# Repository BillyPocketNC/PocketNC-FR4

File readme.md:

# Support for this Project has been discontinued
This is an open source project and is not commercially supported.

For more information and files see [our Wiki](https://pocketnc.atlassian.net/wiki/spaces/PNFUR/pages/368902363/FR4+Resources) for more information

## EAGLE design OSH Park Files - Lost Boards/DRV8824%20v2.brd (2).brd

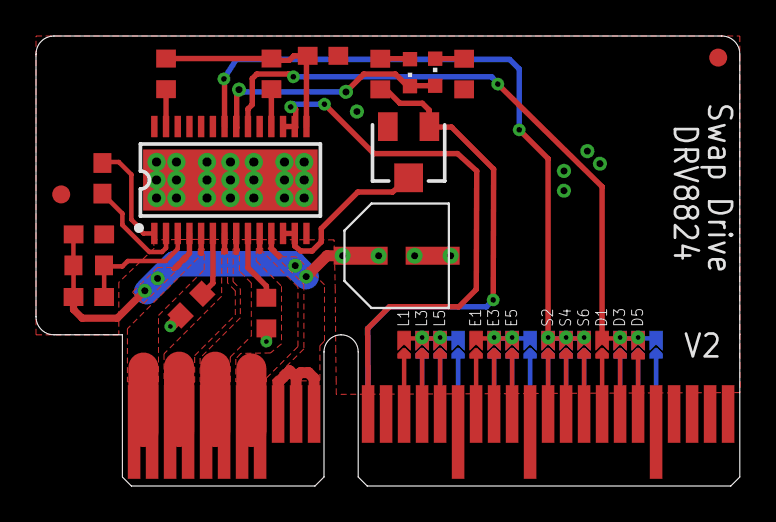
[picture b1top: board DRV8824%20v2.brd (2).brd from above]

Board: 2 copper layers, 39.1 x 25.0 mm, 19 parts (0 on the bottom side), 22 nets.

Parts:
BLU1: CHIPLED_0603
C3: 4.7uf; C0603
C9: .01uf; C0603
C10, C11: .1uf; C0603
DRV8824: DRV8824; HTSSOP-28
GRN1: CHIPLED_0603
R1, R9: 460; R0603
R2, R3: 10k; R0603
R4: .33 ohm; R0603
R5: .33ohm; R0603
R6: 1m; R0603
R22: 10K; TRIMPOT-3MM-2
U$2: PCIE_64_SMART_BOARD
U$7: EEEFK0J220R
U$9, U$12: FIDUCIAL; FIDUCIAL_1MM

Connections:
3.3V: C3.1, DRV8824.15, R2.2, R3.2
3V: R1.2, R22.1, U$2.P$12
5V: DRV8824.16, DRV8824.17, U$2.P$44
DIR: DRV8824.20, U$2.P$57@1
ENBL: BLU1.A, DRV8824.21, GRN1.C
GND: C3.2, C10.2, DRV8824.14, DRV8824.28, DRV8824.GND@10, DRV8824.GND@11, DRV8824.GND@12, DRV8824.GND@13, DRV8824.GND@14, DRV8824.GND@15, DRV8824.GND@16, DRV8824.GND@17, DRV8824.GND@18, DRV8824.GND@19, DRV8824.GND@20, DRV8824.GND@21, DRV8824.GND@22, DRV8824.GND@23, DRV8824.GND@24, DRV8824.GND@25, DRV8824.GND@26, DRV8824.GND@27, DRV8824.GND@28, DRV8824.GND@29, DRV8824.GND@30, DRV8824.GND@PAD, R4.1, R5.1, R9.2, R22.3, U$2.GND@1, U$2.GND@2, U$2.GND@3, U$2.P$13, U$2.P$25, U$2.P$49, U$2.P$53, U$2.P$60, U$7.GND@1, U$7.GND@2, U$7.GND@3
unnamed: C9.2, DRV8824.1
unnamed: C9.1, DRV8824.2
unnamed: DRV8824.18, R2.1
unnamed: DRV8824.9, R5.2
unnamed: DRV8824.6, R4.2
unnamed: BLU1.C, R9.1
unnamed: GRN1.A, R1.1
unnamed: DRV8824.12, DRV8824.13, R22.2
unnamed: DRV8824.27, R3.1
PHASE1: DRV8824.5, U$2.P$33, U$2.P$34
PHASE2: DRV8824.7, U$2.P$35, U$2.P$36
PHASE3: DRV8824.8, U$2.P$37, U$2.P$38
PHASE4: DRV8824.10, U$2.P$39, U$2.P$40
STEP: DRV8824.22, U$2.P$22@1
VCC: C10.1, C11.1, DRV8824.4, DRV8824.11, R6.1, U$2.VCC@1, U$2.VCC@2, U$2.VCC@3, U$7.P$1, U$7.P$3, U$7.P$5
VCP: C11.2, DRV8824.3, R6.2

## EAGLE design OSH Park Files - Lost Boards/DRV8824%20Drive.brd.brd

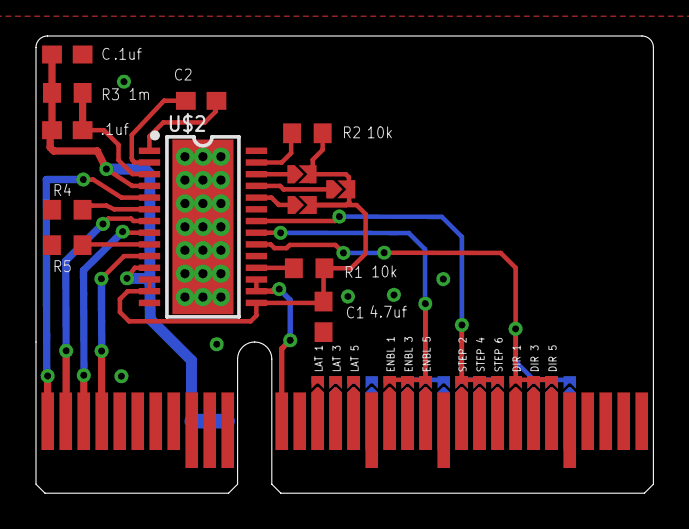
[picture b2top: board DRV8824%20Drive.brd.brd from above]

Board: 2 copper layers, 34.3 x 25.4 mm, 14 parts (0 on the bottom side), 22 nets.

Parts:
10NF2: .1uf; C0603
C: .1uf; C0603
C1: 4.7uf; C0603
C2: .01uf; C0603
R1, R2: 10k; R0603
R3: 1m; R0603
R4, R5: R0603
U$1: PCIE_64_SMART_BOARD
U$2: DRV8824; HTSSOP-28
U$3, U$4, U$5: SELECTIVE_CONNECT

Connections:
3.3V: C1.1, U$2.12, U$2.13, U$2.15
3V: R1.2, R2.2, U$3.P$2, U$4.P$2, U$5.P$2
5V: U$1.P$44, U$2.16, U$2.17
A1: U$1.P$33, U$2.5
A2: U$1.P$34, U$2.7
B1: U$1.P$36, U$2.10
B2: U$1.P$35, U$2.8
DIR: U$1.P$26@1, U$1.P$27@1, U$1.P$28@1, U$1.P$57@1, U$1.P$58@1, U$1.P$59@1, U$2.20
ENBL: U$1.P$19@1, U$1.P$20@1, U$1.P$21@1, U$1.P$50@1, U$1.P$51@1, U$1.P$52@1, U$2.21
GND: C.2, C1.2, R4.1, R5.1, U$1.GND@1, U$1.GND@2, U$1.GND@3, U$1.P$13, U$1.P$25, U$1.P$49, U$1.P$53, U$1.P$60, U$2.14, U$2.28, U$2.GND@10, U$2.GND@11, U$2.GND@12, U$2.GND@13, U$2.GND@14, U$2.GND@15, U$2.GND@16, U$2.GND@17, U$2.GND@18, U$2.GND@19, U$2.GND@20, U$2.GND@21, U$2.GND@22, U$2.GND@23, U$2.GND@24, U$2.GND@25, U$2.GND@26, U$2.GND@27, U$2.GND@28, U$2.GND@29, U$2.GND@30, U$2.GND@PAD
unnamed: C2.2, U$2.1
unnamed: C2.1, U$2.2
unnamed: R5.2, U$2.9
unnamed: R1.1, U$2.18
unnamed: R4.2, U$2.6
unnamed: R2.1, U$2.27
unnamed: U$2.26, U$3.P$1
unnamed: U$2.25, U$4.P$1
unnamed: U$2.24, U$5.P$1
STEP: U$1.P$22@1, U$1.P$23@1, U$1.P$24@1, U$1.P$54@1, U$1.P$55@1, U$1.P$56@1, U$2.22
VCC: 10NF2.1, C.1, R3.1, U$1.P$9, U$1.P$10, U$1.P$11, U$2.4, U$2.11
VCP: 10NF2.2, R3.2, U$2.3

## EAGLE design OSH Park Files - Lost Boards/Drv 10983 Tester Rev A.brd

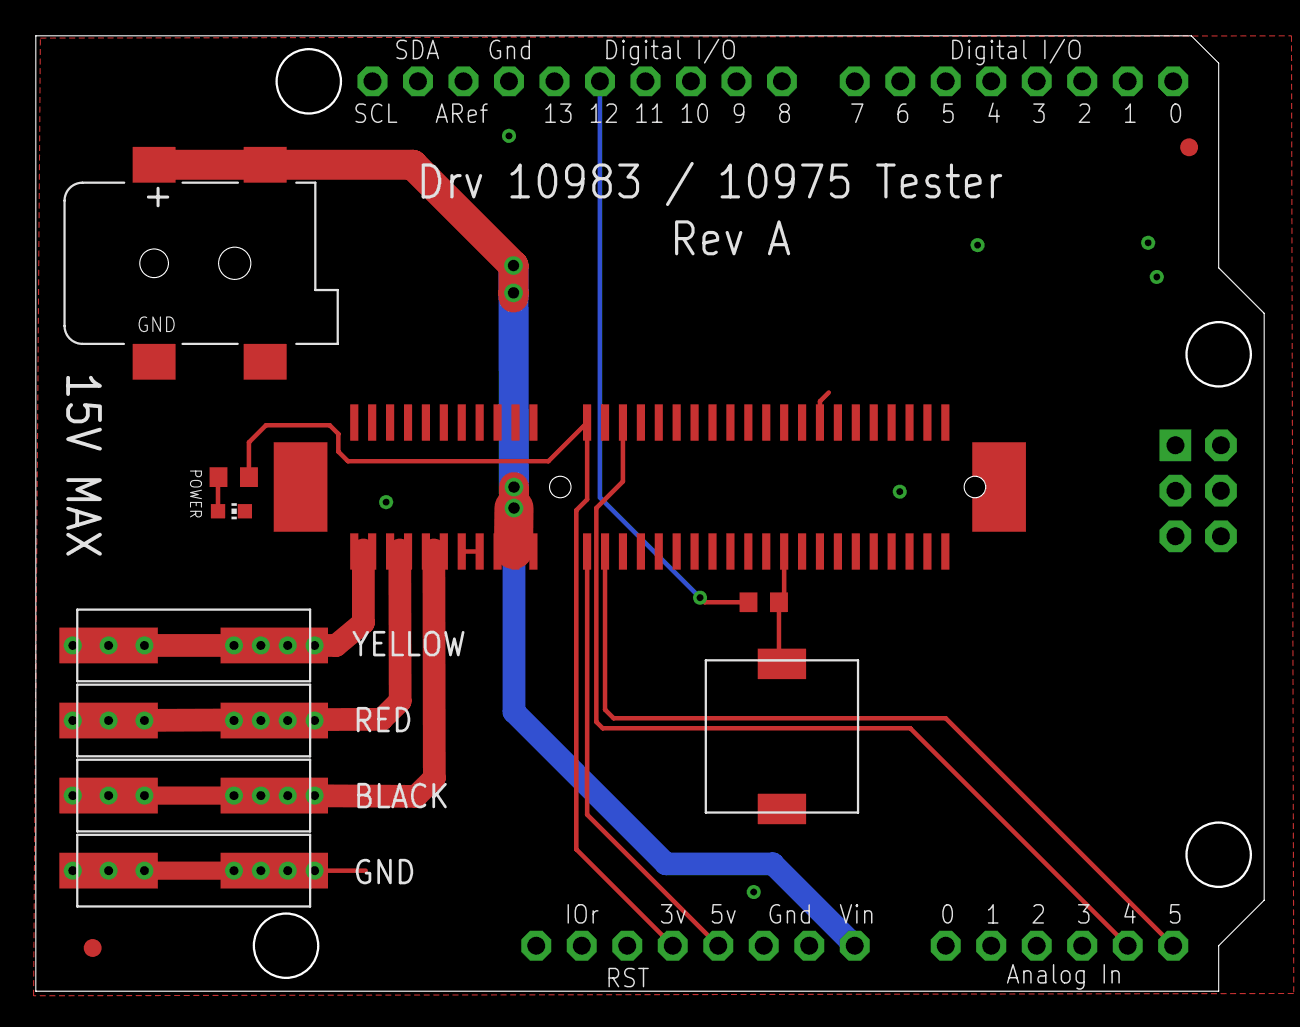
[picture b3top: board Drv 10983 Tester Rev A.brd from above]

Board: 2 copper layers, 68.5 x 53.2 mm, 13 parts (0 on the bottom side), 13 nets.

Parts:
BLACK: 104188-0110
CN1: DCJACK_2MM_SMT
GND: 104188-0110
M2: ARDUINO_R3_ICSP; ARDUINOR3_ICSP
POWER: CHIP-LED0603
R1: 460; R0603
R2: 220; R0603
RED: 104188-0110
U$1: 10061913-101CLF; 10076266-100CLF
U$2, U$3: FIDUCIAL; FIDUCIAL_1MM
U$4: BUTTON_SKSTAAE010
YELLOW: 104188-0110

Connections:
3V: M2.3V, R1.1, U$1.P$12
5V: M2.5V, U$1.P$44
ENBL: R2.1, U$1.P$55, U$4.P$1
GND: CN1.GND, CN1.GNDBREAK, GND.1@1, M2.GND, M2.GND@1, M2.GND@3, POWER.C, U$1.P$9, U$1.P$10, U$1.P$11, U$1.P$13, U$1.P$25, U$1.P$49, U$1.P$53, U$1.P$60, U$4.P$2
unnamed: POWER.A, R1.2
unnamed: M2.D12, R2.2
O: U$1.P$39, U$1.P$40
SCL: M2.A5, U$1.P$45
SDA: M2.A4, U$1.P$14
U: U$1.P$33, U$1.P$34, YELLOW.1@1
V: RED.1@1, U$1.P$35, U$1.P$36
VCC: CN1.PWR1, M2.VIN, U$1.P$41, U$1.P$42, U$1.P$43
W: BLACK.1@1, U$1.P$37, U$1.P$38

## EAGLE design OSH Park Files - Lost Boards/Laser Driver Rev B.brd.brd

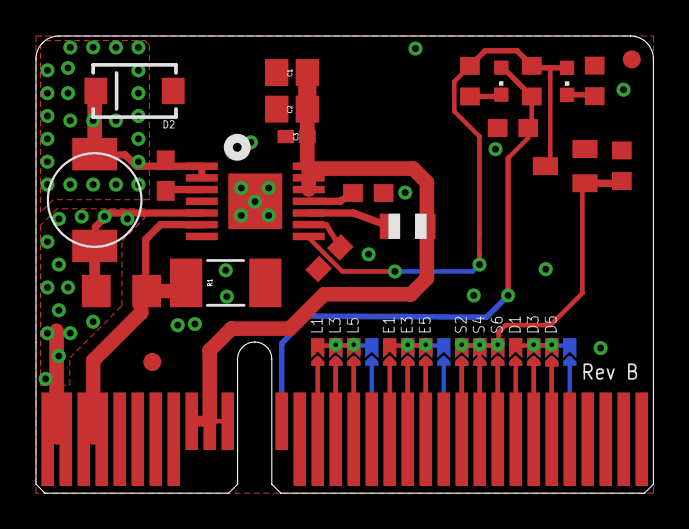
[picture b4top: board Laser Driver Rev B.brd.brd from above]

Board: 2 copper layers, 34.3 x 25.4 mm, 23 parts (0 on the bottom side), 14 nets.

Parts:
2N7002P: SOT23
C1, C2: 10uf; C0805
C3: C0402K
C11: .1uf; C0603
CB: 22nf; C0603
CC: 100nf; C0603
CF: 100nf; C0603
CO: C1206
D2: B340A; SMA-DIODE
GRN: CHIPLED_0603
R1: .166; R2010
R3, R7, R9: 460; R0603
R6: 10k; R0603
R-ON: 148k; R0805
RED: CHIPLED_0603
U$1: LM3406; HTSSOP-14
U$2: PCIE_64_SMART_BOARD
U$5, U$6: FIDUCIAL; FIDUCIAL_1MM
U$7: L-13uH; LQH55

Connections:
3V: C11.2, GRN.A, R7.2, U$2.P$12
ENBL-IN: 2N7002P.1, R6.2, U$2.P$22@1
ENBL-OUT: 2N7002P.3, R7.1, R9.2, RED.A, U$1.P$8
GND: 2N7002P.2, C1.2, C2.2, C3.2, C11.1, CC.1, CF.1, D2.A, R1.1, R3.2, R6.1, U$1.P$7, U$1.P$15, U$2.GND@1, U$2.GND@2, U$2.GND@3, U$2.P$13, U$2.P$25, U$2.P$49, U$2.P$53, U$2.P$60
LS+: CO.1, U$1.P$5, U$2.P$33, U$2.P$34, U$7.2
LS-: CO.2, R1.2, U$1.P$6, U$2.P$35, U$2.P$36
unnamed: CB.1, U$1.P$3
unnamed: GRN.C, R9.1
unnamed: R3.1, RED.C
unnamed: CC.2, U$1.P$9
unnamed: CF.2, U$1.P$11
RON: R-ON.1, U$1.P$10
SW: CB.2, D2.C, U$1.P$1, U$1.P$2, U$7.1
VCC: C1.1, C2.1, C3.1, R-ON.2, U$1.P$12, U$1.P$13, U$1.P$14, U$2.VCC@1, U$2.VCC@2, U$2.VCC@3

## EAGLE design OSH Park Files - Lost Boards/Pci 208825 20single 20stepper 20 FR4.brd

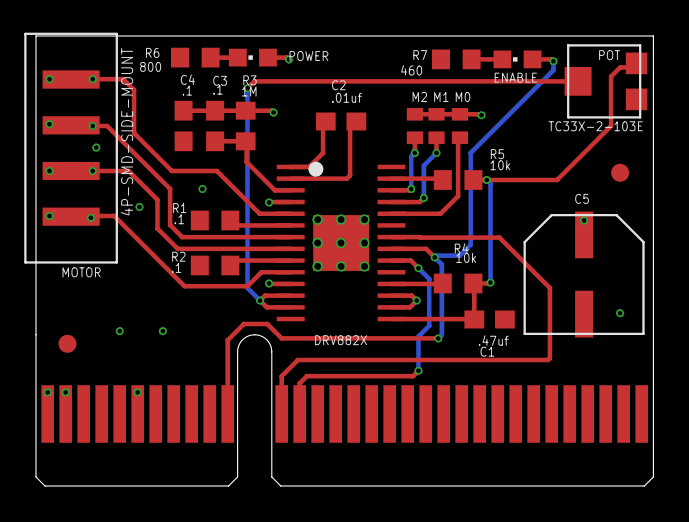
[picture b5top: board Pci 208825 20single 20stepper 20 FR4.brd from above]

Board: 4 copper layers, 34.3 x 25.0 mm, 23 parts (0 on the bottom side), 24 nets.

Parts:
C1: .47uf; C0603
C2: .01uf; C0603
C3, C4: .1; C0603
C5: EEEFTH101XAP
DRV882X: DRV8825
ENABLE: CHIPLED_0603
M0, M1, M2: R0402
MOTOR: 4P-SMD-SIDE-MOUNT
POT: TC33X-2-103E
POWER: CHIPLED_0603
R1, R2: .1; R0603
R3: 1M; R0603
R4, R5: 10k; R0603
R6: 800; R0603
R7: 460; R0603
U$1: 64P-PCI-EXPRESS
U$2, U$3: FIDUCIAL; FIDUCIAL_1MM

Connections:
+3.3V: C1.1, DRV882X.P$15, POT.P$2, R4.2, R5.2
+5V: DRV882X.P$16, DRV882X.P$17, M0.2, M1.2, M2.2, POWER.A, U$1.P$6, U$1.P$59
A1: DRV882X.P$5, MOTOR.P$1
A2: DRV882X.P$7, MOTOR.P$2
B1: DRV882X.P$10, MOTOR.P$4
B2: DRV882X.P$8, MOTOR.P$3
DIR: DRV882X.P$20, U$1.P$13
ENBL1: DRV882X.P$21, ENABLE.A, U$1.P$11
GND: C1.2, C4.2, C5.P$2, DRV882X.GND, DRV882X.GND@1, DRV882X.GND@2, DRV882X.GND@4, DRV882X.GND@5, DRV882X.GND@6, DRV882X.GND@7, DRV882X.GND@8, DRV882X.GND@9, DRV882X.P$14, DRV882X.P$28, DRV882X.P$29, POT.P$1, R1.1, R2.1, R6.1, R7.1, U$1.P$3, U$1.P$4, U$1.P$61, U$1.P$62
unnamed: DRV882X.P$26, M2.1
unnamed: DRV882X.P$25, M1.1
unnamed: DRV882X.P$24, M0.1
unnamed: DRV882X.P$18, R4.1
unnamed: POWER.C, R6.2
unnamed: ENABLE.C, R7.2
unnamed: DRV882X.P$27, R5.1
unnamed: C2.2, DRV882X.P$1
unnamed: C2.1, DRV882X.P$2
unnamed: C3.1, DRV882X.P$3, R3.2
unnamed: DRV882X.P$6, R1.2
unnamed: DRV882X.P$9, R2.2
STEP: DRV882X.P$22, U$1.P$12
VDD: C3.2, C4.1, C5.P$1, DRV882X.P$4, DRV882X.P$11, R3.1, U$1.P$1, U$1.P$2, U$1.P$63, U$1.P$64
VREF: DRV882X.P$12, DRV882X.P$13, POT.P$3

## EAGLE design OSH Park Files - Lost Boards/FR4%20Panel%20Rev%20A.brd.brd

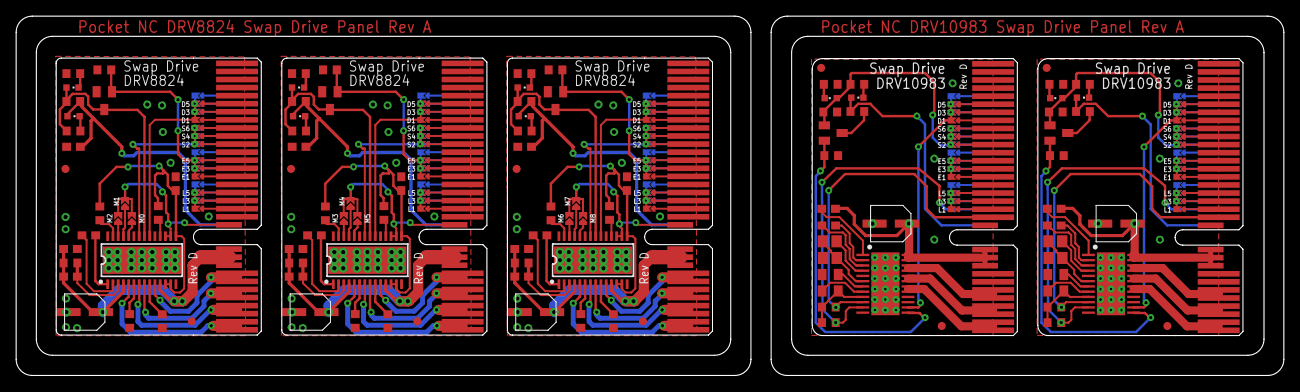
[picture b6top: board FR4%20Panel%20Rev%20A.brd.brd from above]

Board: 2 copper layers, 157.0 x 44.5 mm, 117 parts (0 on the bottom side), 117 nets.

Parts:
2N7002P, 2N7002P1, 2N7002P2, 2N7002P3, 2N7002P4: SOT23
C1, C11, C16: 4.7uf; C0603
C2, C3, C8, C9, C10, C13, C14, C15, C18, C19, C20, C21, C22: .1uf; C0603
C4, C7, C24, C25: C0805K
C5, C23: 10uf; C0805
C6, C12, C17: .01uf; C0603
DRV1, DRV2, DRV8824: DRV8824; HTSSOP-28
GRN, GRN1, GRN2, GRN3, GRN4: CHIPLED_0603
L1, L2: 47uh; C0805
M0, M1, M2, M3, M4, M5, M6, M7, M8: SELECTIVE_CONNECT
R1, R2, R35, R36: 5k; R0603
R3, R10, R11, R14, R15, R16, R23, R24, R25, R32, R33, R34, R37, R40, R41: 460; R0603
R4, R5, R6, R7, R13, R17, R18, R22, R26, R27, R31, R38, R39: 10k; R0603
R8, R9, R19, R20, R28, R29: R0603
R12, R21, R30: 1m; R0603
RED, RED1, RED2, RED3, RED4: CHIPLED_0603
U$1, U$6, U$10, U$14, U$18: PCIE_64_SMART_BOARD
U$2, U$19: DRV10983; HTSS0P-24
U$3, U$20: 10uf; EEEFK0J220R
U$4, U$5, U$8, U$9, U$12, U$13, U$16, U$17, U$21, U$22: FIDUCIAL; FIDUCIAL_1MM
U$7, U$11, U$15: EEEFK0J220R

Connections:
3.3V: C1.1, DRV8824.12, DRV8824.13, DRV8824.15, R6.2, R7.2
3.3V1: C11.1, DRV1.12, DRV1.13, DRV1.15, R17.2, R18.2
3.3V2: C16.1, DRV2.12, DRV2.13, DRV2.15, R26.2, R27.2
3V: GRN1.A, R3.2, U$1.P$12
3V1: C10.2, GRN.A, R14.2, U$6.P$12
3V2: C15.2, GRN2.A, R23.2, U$10.P$12
3V3: C20.2, GRN3.A, R32.2, U$14.P$12
3V4: GRN4.A, R37.2, U$18.P$12
5V: DRV8824.16, DRV8824.17, M0.P$2, M1.P$2, M2.P$2, U$6.P$44
5V1: DRV1.16, DRV1.17, M3.P$2, M4.P$2, M5.P$2, U$10.P$44
5V2: DRV2.16, DRV2.17, M6.P$2, M7.P$2, M8.P$2, U$14.P$44
A1: DRV8824.5, U$6.P$33, U$6.P$34
A2: DRV8824.7, U$6.P$35, U$6.P$36
A3: DRV1.5, U$10.P$33, U$10.P$34
A4: DRV1.7, U$10.P$35, U$10.P$36
A5: DRV2.5, U$14.P$33, U$14.P$34
A6: DRV2.7, U$14.P$35, U$14.P$36
B1: DRV8824.10, U$6.P$39, U$6.P$40
B2: DRV8824.8, U$6.P$37, U$6.P$38
B3: DRV1.8, U$10.P$37, U$10.P$38
B4: DRV1.10, U$10.P$39, U$10.P$40
B5: DRV2.8, U$14.P$37, U$14.P$38
B6: DRV2.10, U$14.P$39, U$14.P$40
DIR: U$1.P$57@1, U$2.P$14
DIR1: DRV8824.20, U$6.P$57@1
DIR2: DRV1.20, U$10.P$57@1
DIR3: DRV2.20, U$14.P$57@1
DIR4: U$18.P$57@1, U$19.P$14
ENBL: 2N7002P1.1, R4.2, R11.2, RED1.A, U$1.P$22@1
ENBL1: 2N7002P4.1, R38.2, R41.2, RED4.A, U$18.P$22@1
ENBL-IN: 2N7002P.1, R13.2, U$6.P$50@1
ENBL-IN1: 2N7002P2.1, R22.2, U$10.P$50@1
ENBL-IN2: 2N7002P3.1, R31.2, U$14.P$50@1
ENBL-OUT: 2N7002P.3, DRV8824.21, R14.1, R16.2, RED.A
ENBL-OUT1: 2N7002P2.3, DRV1.21, R23.1, R25.2, RED2.A
ENBL-OUT2: 2N7002P3.3, DRV2.21, R32.1, R34.2, RED3.A
GND: C4.1, C5.1, C7.1, R4.1, R5.2, R10.2, U$1.GND@1, U$1.GND@2, U$1.GND@3, U$1.P$13, U$1.P$25, U$1.P$49, U$1.P$53, U$1.P$60, U$2.GND, U$2.GND@1, U$2.GND@3, U$2.GND@4, U$2.GND@5, U$2.GND@6, U$2.GND@7, U$2.GND@8, U$2.GND@9, U$2.GND@10, U$2.GND@11, U$2.GND@12, U$2.GND@13, U$2.GND@14, U$2.GND@15, U$2.GND@16, U$2.GND@17, U$2.GND@18, U$2.GND@19, U$2.GND@20, U$2.P$5, U$2.P$8, U$2.P$15, U$2.P$16, U$3.GND@2
GND1: 2N7002P.2, C1.2, C8.2, C10.1, DRV8824.14, DRV8824.28, DRV8824.GND@10, DRV8824.GND@11, DRV8824.GND@12, DRV8824.GND@13, DRV8824.GND@14, DRV8824.GND@15, DRV8824.GND@16, DRV8824.GND@17, DRV8824.GND@18, DRV8824.GND@19, DRV8824.GND@20, DRV8824.GND@21, DRV8824.GND@22, DRV8824.GND@23, DRV8824.GND@24, DRV8824.GND@25, DRV8824.GND@26, DRV8824.GND@27, DRV8824.GND@28, DRV8824.GND@29, DRV8824.GND@30, DRV8824.GND@PAD, R8.1, R9.1, R13.1, R15.2, U$6.GND@1, U$6.GND@2, U$6.GND@3, U$6.P$13, U$6.P$25, U$6.P$49, U$6.P$53, U$6.P$60, U$7.GND@2
GND2: 2N7002P2.2, C11.2, C13.2, C15.1, DRV1.14, DRV1.28, DRV1.GND@10, DRV1.GND@11, DRV1.GND@12, DRV1.GND@13, DRV1.GND@14, DRV1.GND@15, DRV1.GND@16, DRV1.GND@17, DRV1.GND@18, DRV1.GND@19, DRV1.GND@20, DRV1.GND@21, DRV1.GND@22, DRV1.GND@23, DRV1.GND@24, DRV1.GND@25, DRV1.GND@26, DRV1.GND@27, DRV1.GND@28, DRV1.GND@29, DRV1.GND@30, DRV1.GND@PAD, R19.1, R20.1, R22.1, R24.2, U$10.GND@1, U$10.GND@2, U$10.GND@3, U$10.P$13, U$10.P$25, U$10.P$49, U$10.P$53, U$10.P$60, U$11.GND@2
GND3: 2N7002P3.2, C16.2, C18.2, C20.1, DRV2.14, DRV2.28, DRV2.GND@10, DRV2.GND@11, DRV2.GND@12, DRV2.GND@13, DRV2.GND@14, DRV2.GND@15, DRV2.GND@16, DRV2.GND@17, DRV2.GND@18, DRV2.GND@19, DRV2.GND@20, DRV2.GND@21, DRV2.GND@22, DRV2.GND@23, DRV2.GND@24, DRV2.GND@25, DRV2.GND@26, DRV2.GND@27, DRV2.GND@28, DRV2.GND@29, DRV2.GND@30, DRV2.GND@PAD, R28.1, R29.1, R31.1, R33.2, U$14.GND@1, U$14.GND@2, U$14.GND@3, U$14.P$13, U$14.P$25, U$14.P$49, U$14.P$53, U$14.P$60, U$15.GND@2
GND4: C23.1, C24.1, C25.1, R38.1, R39.2, R40.2, U$18.GND@1, U$18.GND@2, U$18.GND@3, U$18.P$13, U$18.P$25, U$18.P$49, U$18.P$53, U$18.P$60, U$19.GND, U$19.GND@1, U$19.GND@3, U$19.GND@4, U$19.GND@5, U$19.GND@6, U$19.GND@7, U$19.GND@8, U$19.GND@9, U$19.GND@10, U$19.GND@11, U$19.GND@12, U$19.GND@13, U$19.GND@14, U$19.GND@15, U$19.GND@16, U$19.GND@17, U$19.GND@18, U$19.GND@19, U$19.GND@20, U$19.P$5, U$19.P$8, U$19.P$15, U$19.P$16, U$20.GND@2
unnamed: C2.2, U$2.P$1
unnamed: C3.2, U$2.P$2
unnamed: C3.1, U$2.P$3
unnamed: DRV8824.6, R8.2
unnamed: R10.1, RED1.C
unnamed: C4.2, U$2.P$7
unnamed: C6.2, DRV8824.1
unnamed: GRN1.C, R11.1
unnamed: 2N7002P1.3, R3.1
unnamed: C6.1, DRV8824.2
unnamed: DRV8824.9, R9.2
unnamed: DRV8824.18, R6.1
unnamed: GRN.C, R16.1
unnamed: R15.1, RED.C
unnamed: DRV1.6, R19.2
unnamed: DRV8824.27, R7.1
unnamed: DRV8824.26, M2.P$1
unnamed: DRV8824.25, M1.P$1
unnamed: DRV8824.24, M0.P$1
unnamed: DRV1.27, R18.1
unnamed: DRV1.26, M3.P$1
unnamed: DRV1.25, M4.P$1
unnamed: DRV1.24, M5.P$1
unnamed: C12.2, DRV1.1
unnamed: C12.1, DRV1.2
unnamed: DRV1.9, R20.2
unnamed: DRV1.18, R17.1
unnamed: GRN2.C, R25.1
unnamed: R24.1, RED2.C
unnamed: DRV2.6, R28.2
unnamed: DRV2.27, R27.1
unnamed: DRV2.26, M6.P$1
unnamed: DRV2.25, M7.P$1
unnamed: DRV2.24, M8.P$1
unnamed: C17.2, DRV2.1
unnamed: C17.1, DRV2.2
unnamed: DRV2.9, R29.2
unnamed: DRV2.18, R26.1
unnamed: GRN3.C, R34.1
unnamed: R33.1, RED3.C
unnamed: C21.2, U$19.P$1
unnamed: C22.2, U$19.P$2
unnamed: C22.1, U$19.P$3
unnamed: C25.2, U$19.P$7
unnamed: 2N7002P4.3, R37.1
unnamed: R40.1, RED4.C
unnamed: GRN4.C, R41.1
PWM: 2N7002P1.2, R5.1, U$2.P$13
PWM1: 2N7002P4.2, R39.1, U$19.P$13
SCL: R1.2, U$1.P$45, U$2.P$10
SCL1: R35.2, U$18.P$45, U$19.P$10
SDA: R2.2, U$1.P$14, U$2.P$11
SDA1: R36.2, U$18.P$14, U$19.P$11
STEP: DRV8824.22, U$6.P$22@1
STEP1: DRV1.22, U$10.P$22@1
STEP2: DRV2.22, U$14.P$22@1
SW: L1.2, U$2.P$4
SW1: L2.2, U$19.P$4
U: U$1.P$33, U$1.P$34, U$2.P$17, U$2.P$18
U1: U$18.P$33, U$18.P$34, U$19.P$17, U$19.P$18
V: U$1.P$35, U$1.P$36, U$2.P$19, U$2.P$20
V1: U$18.P$35, U$18.P$36, U$19.P$19, U$19.P$20
V3P1: C24.2, R35.1, R36.1, U$19.P$9
V3P3: C7.2, R1.1, R2.1, U$2.P$9
VCC: C2.1, U$1.VCC@1, U$1.VCC@2, U$1.VCC@3, U$2.P$23, U$2.P$24, U$3.P$3
VCC1: C8.1, C9.1, DRV8824.4, DRV8824.11, R12.1, U$6.VCC@1, U$6.VCC@2, U$6.VCC@3, U$7.P$3
VCC2: C13.1, C14.1, DRV1.4, DRV1.11, R21.1, U$10.VCC@1, U$10.VCC@2, U$10.VCC@3, U$11.P$3
VCC3: C18.1, C19.1, DRV2.4, DRV2.11, R30.1, U$14.VCC@1, U$14.VCC@2, U$14.VCC@3, U$15.P$3
VCC4: C21.1, U$18.VCC@1, U$18.VCC@2, U$18.VCC@3, U$19.P$23, U$19.P$24, U$20.P$3
VCP: C9.2, DRV8824.3, R12.2
VCP1: C14.2, DRV1.3, R21.2
VCP2: C19.2, DRV2.3, R30.2
VREG: C5.2, L1.1, U$2.P$6
VREG1: C23.2, L2.1, U$19.P$6
W: U$1.P$37, U$1.P$38, U$2.P$21, U$2.P$22
W1: U$18.P$37, U$18.P$38, U$19.P$21, U$19.P$22

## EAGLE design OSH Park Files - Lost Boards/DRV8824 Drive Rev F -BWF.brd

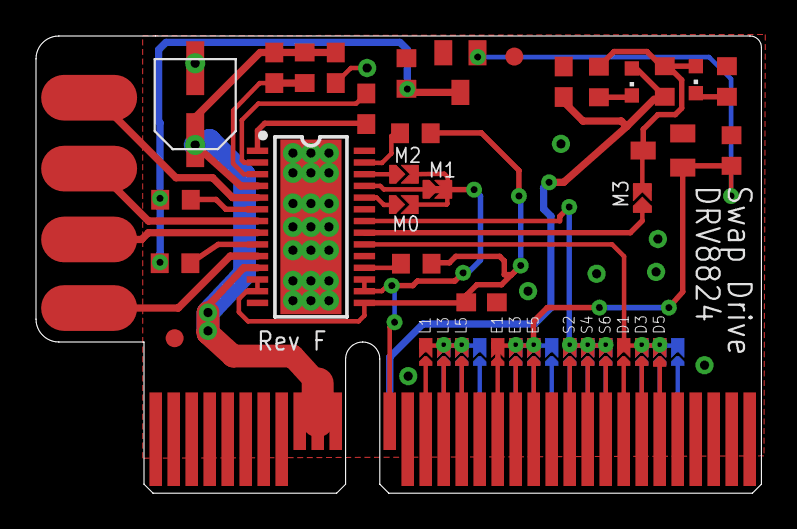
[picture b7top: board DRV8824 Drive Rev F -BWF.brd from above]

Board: 2 copper layers, 40.3 x 25.4 mm, 28 parts (0 on the bottom side), 26 nets.

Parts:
2N7002P, 2N7002P1: SOT23
C1: 4.7uf; C0603
C2: .01uf; C0603
C3, C4, C5: .1uf; C0603
DRV8824: DRV8824; HTSSOP-28
GRN: CHIPLED_0603
M0, M1, M2, M3: SELECTIVE_CONNECT
R1, R2, R6: 10k; R0603
R3: 1m; R0603
R4, R5, R10: R0603
R7, R8, R9: 460; R0603
RED: CHIPLED_0603
U$1: PCIE_64_SMART_BOARD
U$2: EEEFK0J220R
U$4, U$5: FIDUCIAL; FIDUCIAL_1MM

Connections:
3.3V: C1.1, DRV8824.12, DRV8824.13, DRV8824.15, R1.2, R2.2
3V: C5.2, GRN.A, R7.2, U$1.P$12
5V: DRV8824.16, DRV8824.17, M0.P$2, M1.P$2, M2.P$2, U$1.P$44
A1: DRV8824.5, U$1.P$33, U$1.P$34
A2: DRV8824.7, U$1.P$35, U$1.P$36
B1: DRV8824.10, U$1.P$39, U$1.P$40
B2: DRV8824.8, U$1.P$37, U$1.P$38
CHANGE_A: 2N7002P1.3, R4.1, R5.1, R10.2
DIR: DRV8824.20, U$1.P$57@1
ENBL-IN: 2N7002P.1, 2N7002P1.1, R6.2, U$1.P$50@1
ENBL-OUT: 2N7002P.3, DRV8824.21, M3.P$1, M3.P$2, R7.1, R9.2, RED.A
GND: 2N7002P.2, 2N7002P1.2, C1.2, C4.2, C5.1, DRV8824.14, DRV8824.28, DRV8824.GND@10, DRV8824.GND@11, DRV8824.GND@12, DRV8824.GND@13, DRV8824.GND@14, DRV8824.GND@15, DRV8824.GND@16, DRV8824.GND@17, DRV8824.GND@18, DRV8824.GND@19, DRV8824.GND@20, DRV8824.GND@21, DRV8824.GND@22, DRV8824.GND@23, DRV8824.GND@24, DRV8824.GND@25, DRV8824.GND@26, DRV8824.GND@27, DRV8824.GND@28, DRV8824.GND@29, DRV8824.GND@30, DRV8824.GND@PAD, R6.1, R8.2, R10.1, U$1.GND@1, U$1.GND@2, U$1.GND@3, U$1.P$13, U$1.P$25, U$1.P$49, U$1.P$53, U$1.P$60, U$2.GND@2
unnamed: C2.2, DRV8824.1
unnamed: C2.1, DRV8824.2
unnamed: R8.1, RED.C
unnamed: DRV8824.9, R5.2
unnamed: DRV8824.18, R1.1
unnamed: DRV8824.6, R4.2
unnamed: GRN.C, R9.1
unnamed: DRV8824.27, R2.1
unnamed: DRV8824.26, M2.P$1
unnamed: DRV8824.25, M1.P$1
unnamed: DRV8824.24, M0.P$1
STEP: DRV8824.22, U$1.P$22@1
VCC: C3.1, C4.1, DRV8824.4, DRV8824.11, R3.1, U$1.VCC@1, U$1.VCC@2, U$1.VCC@3, U$2.P$3
VCP: C3.2, DRV8824.3, R3.2

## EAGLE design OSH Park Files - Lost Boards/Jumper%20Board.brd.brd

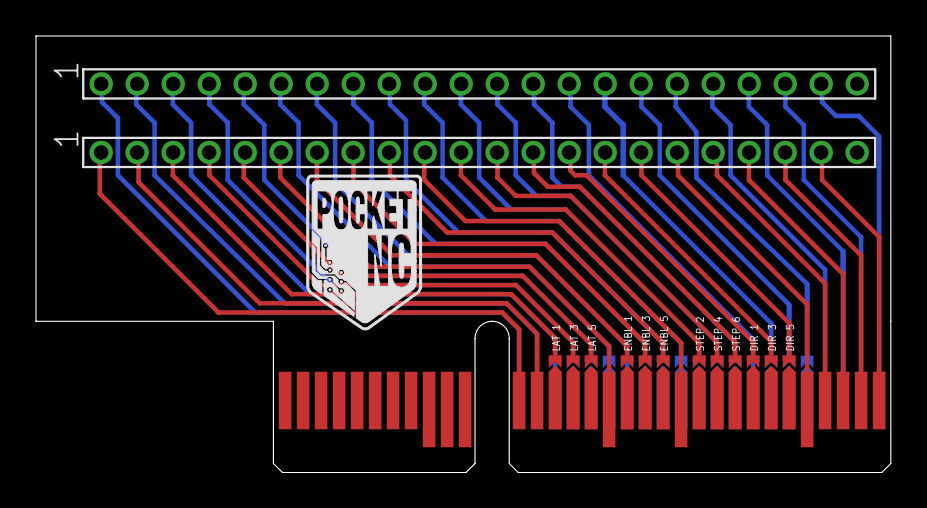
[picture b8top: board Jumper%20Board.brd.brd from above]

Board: 2 copper layers, 47.5 x 24.2 mm, 3 parts (0 on the bottom side), 42 nets.

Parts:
U$1: PCIE_64_SMART_BOARD
U$2, U$3: 1X22THM; 1X22

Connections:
unnamed: U$1.P$44, U$3.1
unnamed: U$1.P$45, U$3.2
unnamed: U$1.P$46@1, U$3.3
unnamed: U$1.P$47@1, U$3.4
unnamed: U$1.P$48@1, U$3.5
unnamed: U$1.P$49, U$3.6
unnamed: U$1.P$50@1, U$3.7
unnamed: U$1.P$51@1, U$3.8
unnamed: U$1.P$52@1, U$3.9
unnamed: U$1.P$53, U$3.10
unnamed: U$1.P$54@1, U$3.11
unnamed: U$1.P$55@1, U$3.12
unnamed: U$1.P$56@1, U$3.13
unnamed: U$1.P$57@1, U$3.14
unnamed: U$1.P$58@1, U$3.15
unnamed: U$1.P$59@1, U$3.16
unnamed: U$1.P$60, U$3.17
unnamed: U$1.P$61, U$3.18
unnamed: U$1.P$62, U$3.19
unnamed: U$1.P$63, U$3.20
unnamed: U$1.P$64, U$3.21
unnamed: U$1.P$12, U$2.1
unnamed: U$1.P$13, U$2.2
unnamed: U$1.P$14, U$2.3
unnamed: U$1.P$15@1, U$2.4
unnamed: U$1.P$16@1, U$2.5
unnamed: U$1.P$17@1, U$2.6
unnamed: U$1.P$18, U$2.7
unnamed: U$1.P$19@1, U$2.8
unnamed: U$1.P$20@1, U$2.9
unnamed: U$1.P$21@1, U$2.10
unnamed: U$1.P$22@1, U$2.11
unnamed: U$1.P$23@1, U$2.12
unnamed: U$1.P$24@1, U$2.13
unnamed: U$1.P$25, U$2.14
unnamed: U$1.P$26@1, U$2.15
unnamed: U$1.P$27@1, U$2.16
unnamed: U$1.P$28@1, U$2.17
unnamed: U$1.P$29, U$2.18
unnamed: U$1.P$30, U$2.19
unnamed: U$1.P$31, U$2.20
unnamed: U$1.P$32, U$2.21

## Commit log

2020-03-31 Kicad Files
2020-03-31 All Fr4 docs + KiCad Conversion
2020-07-23 added missing driver files from OSH Park
2021-06-23 Converted a few of the swapp drive boards to KiCad

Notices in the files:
parts and their libraries:
SparkFun-Electromechanical: Licensing: Creative Commons ShareAlike 4.0 International - https://creativecommons.org/licenses/by-sa/4.0
